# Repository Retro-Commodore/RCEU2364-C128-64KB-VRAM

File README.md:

# RCEU2364-C128-64KB-VRAM
 64KB VRAM upgrade to the C128/C128D (Not C128DCR as it already has)
 
 See more colors, get higher resolutions, Watch Risen to Oblivion demo as it should be seen.
 
 NOTE: this revision is yet not testet, but should work.

# BOM
 Optional  
 2x 18pin DIL Sockets  
 1x 48pin DIL Socket  
 
 Required  
 2x 24pin DIL Male/Male header (preferably turned)  
 22nF ceramic capacitor  
 2x 4464 or 41464 4bit 64K Ram chips  

# How to place components

Carefully pull out the 80 column graphics chip MOS8563, and insert/solder (highly recommended to use a socket) it into the socket of the vram expansion.  
Insert the vram expansion into the socket where the MOS8563 was sitting.

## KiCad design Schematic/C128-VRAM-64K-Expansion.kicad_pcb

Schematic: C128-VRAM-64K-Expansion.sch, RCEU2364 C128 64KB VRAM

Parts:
C1: 22nF; C5B2.5
IC1: MOS8563
IC2: DIL48
IC3, IC4: 41464C; DIL18

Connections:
/B: IC1.44 (B), IC2.44
/CCLK: IC1.1 (CCLK), IC2.1
/CS: IC1.4 (CS), IC2.4
/D0: IC1.18 (D0), IC2.18
/D1: IC1.17 (D1), IC2.17
/D2: IC1.16 (D2), IC2.16
/D3: IC1.15 (D3), IC2.15
/D4: IC1.14 (D4), IC2.14
/D5: IC1.13 (D5), IC2.13
/D6: IC1.11 (D6), IC2.11
/D7: IC1.10 (D7), IC2.10
/DA0: IC1.26 (DA0), IC2.26, IC3.10 (A7), IC4.10 (A7)
/DA1: IC1.27 (DA1), IC2.27, IC3.8 (A4), IC4.8 (A4)
/DA2: IC1.28 (DA2), IC2.28, IC3.11 (A3), IC4.11 (A3)
/DA3: IC1.29 (DA3), IC2.29, IC3.7 (A5), IC4.7 (A5)
/DA4: IC1.30 (DA4), IC2.30, IC3.12 (A2), IC4.12 (A2)
/DA5: IC1.31 (DA5), IC2.31, IC3.6 (A6), IC4.6 (A6)
/DA6: IC1.32 (DA6), IC2.32, IC3.13 (A1), IC4.13 (A1)
/DA7: IC1.33 (DA7), IC2.33, IC3.14 (A0), IC4.14 (A0)
/DD0: IC1.34 (DD0), IC3.15 (I/O3)
/DD1: IC1.35 (DD1), IC3.3 (I/O2)
/DD2: IC1.36 (DD2), IC3.2 (I/O1)
/DD3: IC1.38 (DD3), IC3.17 (I/O4)
/DD4: IC1.39 (DD4), IC4.15 (I/O3)
/DD5: IC1.40 (DD5), IC4.3 (I/O2)
/DD6: IC1.41 (DD6), IC4.2 (I/O1)
/DD7: IC1.42 (DD7), IC4.17 (I/O4)
/DISPEN: IC1.19 (DISPEN), IC2.19
/DR/~W: IC1.21 (DR/~W), IC2.21, IC3.4 (~WE), IC4.4 (~WE)
/G: IC1.45 (G), IC2.45
/HSYNC: IC1.3 (HSYNC), IC2.3
/I: IC1.43 (I), IC2.43
/INIT: IC1.22 (INIT), IC2.22
/LPEN: IC1.25 (LPEN), IC2.25
/N/C: IC1.6 (N/C), IC2.6
/NC: IC1.5 (NC), IC2.5
/R: IC1.46 (R), IC2.46
/R/~W: IC1.9 (R/~W), IC2.9
/TEST: IC1.24 (TEST), IC2.24
/VSYNC: IC1.20 (VSYNC), IC2.20
/~CAS: IC1.48 (~CAS), IC2.48, IC3.16 (~CAS), IC4.16 (~CAS)
/~CS: IC1.7 (~CS), IC2.7
/~DCLK: IC1.2 (~DCLK), IC2.2
/~RAS: IC1.47 (~RAS), IC2.47, IC3.5 (~RAS), IC4.5 (~RAS)
/~RES: IC1.23 (~RES), IC2.23
/~RS: IC1.8 (~RS), IC2.8
GND: C1.2, IC1.12 (VSS), IC2.12, IC3.1 (~OE), IC3.18 (GND), IC4.1 (~OE), IC4.18 (GND)
VCC: C1.1, IC1.37 (VDD), IC2.37, IC3.9 (VCC), IC4.9 (VCC)

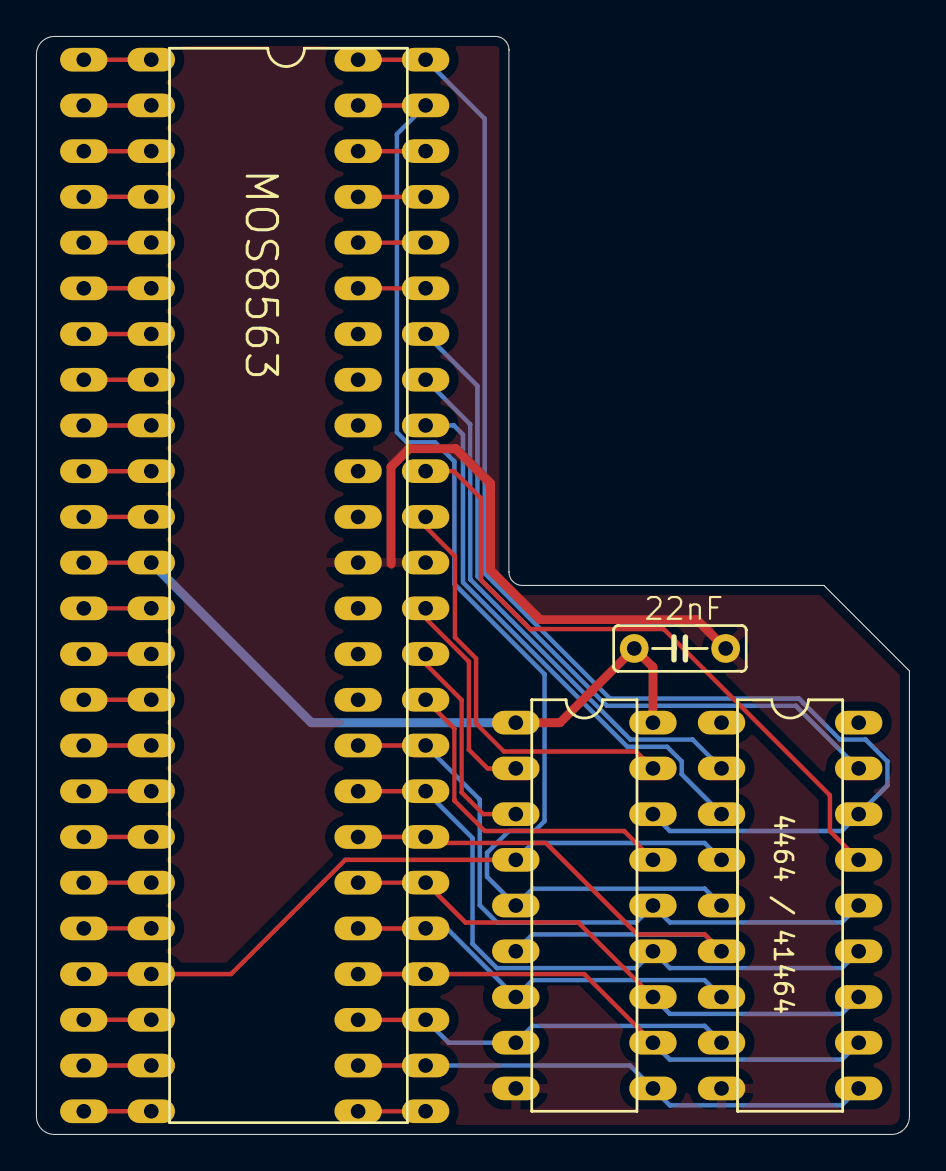
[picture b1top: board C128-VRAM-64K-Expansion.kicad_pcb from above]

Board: 2 copper layers, 48.5 x 61.0 mm, 5 parts (0 on the bottom side), 48 nets.

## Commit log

2021-01-10 Documentation added
2021-04-20 v1.2

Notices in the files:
Schematic/C128-VRAM-64K-Expansion.kicad_pcb:
Copyright (c) 2018-2021
